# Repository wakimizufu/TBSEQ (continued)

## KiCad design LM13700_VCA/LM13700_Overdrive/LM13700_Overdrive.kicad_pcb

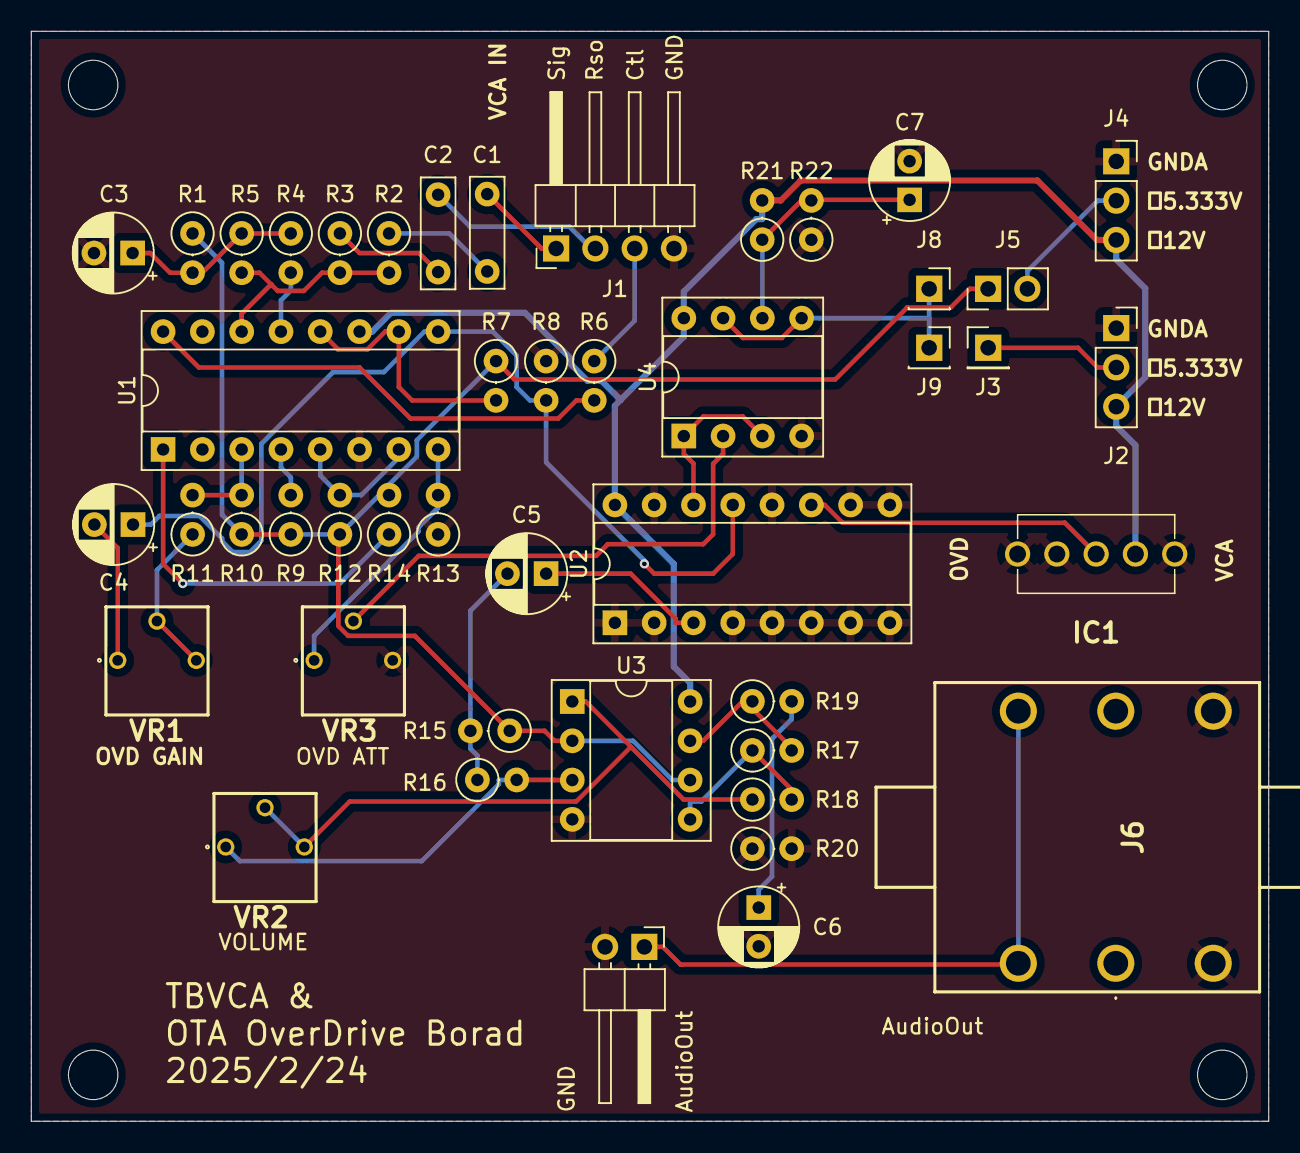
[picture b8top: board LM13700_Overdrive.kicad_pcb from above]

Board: 2 copper layers, 80.0 x 70.5 mm, 46 parts (0 on the bottom side), 36 nets.

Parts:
C1, C2: 0.01uF; C_Rect_L7.0mm_W2.0mm_P5.00mm
C3, C4: 10uF/25V; CP_Radial_D5.0mm_P2.50mm
C5, C6: 1uF/25V; CP_Radial_D5.0mm_P2.50mm
C7: 2.2uF/25V; CP_Radial_D5.0mm_P2.50mm
IC1: 2MS1T1B4VS2QES
J1: Conn_01x04; PinHeader_1x04_P2.54mm_Horizontal
J2, J4: Conn_01x03; PinSocket_1x03_P2.54mm_Vertical
J3: Conn_01x01; PinHeader_1x01_P2.54mm_Vertical
J5: Conn_01x02; PinHeader_1x02_P2.54mm_Vertical
J6: MJ-462; MJ462
J7: Conn_01x02; PinHeader_1x02_P2.54mm_Horizontal
J8, J9: Conn_01x01; PinSocket_1x01_P2.54mm_Vertical
R1, R4, R5: 2.2K; R_Axial_DIN0207_L6.3mm_D2.5mm_P2.54mm_Vertical
R2: 220K; R_Axial_DIN0207_L6.3mm_D2.5mm_P2.54mm_Vertical
R3, R15, R20: 100K; R_Axial_DIN0207_L6.3mm_D2.5mm_P2.54mm_Vertical
R6: 47K; R_Axial_DIN0207_L6.3mm_D2.5mm_P2.54mm_Vertical
R7, R12: 33K; R_Axial_DIN0207_L6.3mm_D2.5mm_P2.54mm_Vertical
R8, R13: 5K; R_Axial_DIN0207_L6.3mm_D2.5mm_P2.54mm_Vertical
R9, R10: 510; R_Axial_DIN0207_L6.3mm_D2.5mm_P2.54mm_Vertical
R11: 1K; R_Axial_DIN0207_L6.3mm_D2.5mm_P2.54mm_Vertical
R14, R16, R17, R18: 10K; R_Axial_DIN0207_L6.3mm_D2.5mm_P2.54mm_Vertical
R19: 100; R_Axial_DIN0207_L6.3mm_D2.5mm_P2.54mm_Vertical
R21: 30K; R_Axial_DIN0207_L6.3mm_D2.5mm_P2.54mm_Vertical
R22: 24K; R_Axial_DIN0207_L6.3mm_D2.5mm_P2.54mm_Vertical
U1: LM13700; DIP-16_W7.62mm_Socket
U2: 4051; DIP-16_W7.62mm_Socket
U3, U4: Opamp_Dual; DIP-8_W7.62mm_Socket
VR1, VR2, VR3: 3362P-1-104LF 100K; 3362P_1

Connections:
+5.333VA: J5.1, R1.1, R7.1, R9.1, R10.1, R12.1, R14.2, R15.1, U3.2 (-), U3.6 (-)
+12VA: IC1.3, J2.3, J4.3, R21.2, U1.11 (V+), U2.16 (VDD), U3.8 (V+), U4.8 (V+)
A+_VCA_Control: J1.3, R6.1
A+_VCA_Resonance: C2.1, J1.2
A+_VCA_Signal: C1.1, J1.1
AUDIO_OUT: C5.1, U2.3 (X)
GNDA: C3.2, C6.2, C7.2, IC1.1, IC1.MH1, IC1.MH2, J1.4, J2.1, J4.1, J6.S1, J6.SS1, J7.2, R8.1, R13.1, R20.1, R20.2, R22.1, U1.6 (V-), U2.1 (X4), U2.2 (X6), U2.4 (X7), U2.5 (X5), U2.6 (Inh), U2.7 (VEE), U2.8 (VSS), U2.9 (C), U2.10 (B), U2.12 (X3), U2.15 (X2), U3.4 (V-), U4.4 (V-), VR3.3 (CW)
unnamed: C1.2, R2.1
unnamed: C2.2, R3.1
unnamed: C3.1, R1.2, R4.1, R5.1
unnamed: C5.2, R15.2, R16.1
unnamed: C6.1, R19.2
unnamed: J2.2, J3.1
unnamed: J4.2, J5.2
unnamed: J6.T1, J6.TS1, J7.1
unnamed: J8.1, J9.1, U4.5 (+), U4.7
unnamed: R6.2, U1.16
unnamed: R7.2, U1.10, U1.12
unnamed: R12.2, U1.5, U1.7
unnamed: R14.1, U1.1
unnamed: R17.2, R19.1, U3.7
unnamed: R2.2, R3.2, R5.2, U1.14 (+)
unnamed: R4.2, U1.13 (-)
unnamed: R10.2, R11.2, U1.3 (+)
unnamed: R9.2, U1.4 (-)
unnamed: R16.2, U3.3 (+), VR2.1 (CCW)
unnamed: R17.1, R18.2, U3.5 (+)
unnamed: U4.2 (-), VR3.2 (WIPER)
unnamed: C7.1, R21.1, R22.2, U4.6 (-)
unnamed: C4.2, VR1.1 (CCW)
unnamed: R11.1, VR1.2 (WIPER), VR1.3 (CW)
unnamed: R18.1, U3.1, VR2.2 (WIPER), VR2.3 (CW)
unnamed: R13.2, U1.8, VR3.1 (CCW)
OVD_OUT: U2.14 (X1), U4.1, U4.3 (+)
SELECT: IC1.2 (2_Comm), U2.11 (A)
VCA_OUT: C4.1, R8.2, U1.9, U2.13 (X0)

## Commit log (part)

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2024-05-16 testClock
2024-05-16 addVSCode
2024-05-16 matrixLED.h
2024-05-16 matrixLED
2024-05-16 reupload TestSwLed
2024-05-16 matrixSW
2024-05-16 SwitchBox
2024-05-17 20240517
2024-05-20 #define DEBUG_ARDUINO
2024-05-20 IDE2 not support VSCode
2024-05-21 voltage
2024-05-21 vscode setting
2024-05-25 mingw&CMake
2024-05-25 VS2022_CPP
2024-05-26 VS2022 cpp/h分離
2024-05-28 DEBUG_ARDUINO
2024-05-28 arudino ソースファイル整理
2024-05-28 boradConst.h
2024-05-31 pin setup
2024-06-19 setup
2024-06-24 aurudino.h
2024-06-24 convert UTF-8
2024-06-25 add debugMode
2024-07-04 debug
2024-07-05 matrixLED&Switch
2024-07-06 32us
2024-07-08 tempo ADC
2024-07-08 tempo debug
2024-07-09 printf tempo
2024-07-09 debugmode
2024-07-11 debug mode
2024-07-12 debug debugmode
2024-07-12 sequenceList&Index
2024-07-14 debugmode スイッチ押したらLEDマトリクス点灯安定版
2024-07-16 debugmode PMW note/LED acc
2024-07-17 patternmode
2024-07-18 patern play::stop
2024-07-19 paternplay squencemap
2024-07-19 patternmode paternplay run
2024-07-20 patternmode patternplay 一通り完了版
2024-07-20 patternmode paternplay TIE
2024-07-21 patternmode paternWrite
2024-07-22 patternmode paternWrite Ver0.1
2024-07-31 TBSEQ_Borad_V1/FRAM
2024-07-31 loadFRAM
2024-08-01 FRAM WritePattern
2024-08-04 HT16K33 5VOutputBuffer
2024-08-05 HT16K33Panel
2024-08-07 HT16K33 Control
2024-08-07 replace
2024-08-08 HT16K33Panel DRC gaber
2024-08-09 powersupply
2024-08-10 analog_separate
2024-08-20 SeqBox
2024-08-21 SeqBox HT16K33 Fix
    LED表示,Switch読み取りタイミング調整済
2024-08-21 SeqBox Fix
    ステップLED点灯追加
    FRAMライブラリの呼び出しが上手く行かない?
    ⇒SeqBoxだと書き込みメソッド(_writeblock())が呼び出せない
    ⇒代替コードでI2Cコマンド送信でしても反映されず
    ⇒ただしFRAMサンプルプログラムは正常に読み書きできるので回路は問題なさそう
2024-08-22 SeqBox Fix
    ・切り分けの為 class FRAM11の内容をpanelManagerに移植した
    ・matrixSwitch::set 配列指定時に指定外の値に値設定してたので修正してFRAM書き込み確認済
    ・LENMAXを仮実装済
2024-08-22 analog_separate Fix
    DMMT3906->HN4C51J
2024-08-24 HT16K33Panel LevelConvert
    HD74LVC541A で5V->3.3Vへ変換をブレッドボードで確認済
2024-08-25 HT16K33
    MIDI RX動作確認済
2024-08-25 SeqBox Fix
    パターンライト:RUNボタンクリック時の演奏を実装
    ⇒演奏中もステップの編集が出来る様に変更
2024-08-26 SeqBox
    パターンプレイ:演奏時の開始ステップのバグ修正
2024-08-26 SeqBox update
    パターンプレイ/ライト:バンク:バンクA,B,C,Dを仮実装済
2024-08-27 SeqBox Fix
    SyncOut:内部テンポに応じた出力を実装済
    ⇒SyncInは仕様上実装を見送り
2024-08-28 SeqBox fix
    MIDIRecive:コーディング済 デバッグ待ち
2024-08-30 SeqBox Fix
    8/30に何故がコンパイルすると起動直ぐにタイマー割込みが停止してしまう？
    ⇒8/27時点のソースから徐々に切り分けしてしたら何故か正常に動く様になった
    MIDIRx:動作確認済
    SyncOut:原因切り分けの為一旦コードを除外
2024-08-31 SeqBox Fix
    SyncOut:再度実装して動作確認済
    パターンプレイ:テンポ点滅スピードを2倍に変更
2024-09-04 SeqBox fix
    ・アクセントの極性を(ON=0V OFF=5V)に変更
    ・パターンライト:RUN状態での演奏で、ゲート/スライド/アクセントがパターンプレイと異なる状態だったのを修正
2024-09-23 analog_separate fix
    実装してバグを修正
    ・VR6以外のボリュームの左右が逆なのを修正
    ・デュアルトランジスタをHN1C01FU-GRに変更
    ・VCA CA3080後の出力段のバイアス/増幅率等の設計ミスを修正
    ・入力信号のシルク位置が間違っているので修正
    ⇒それ以外は正常動作を確認済
2024-09-29 TBSEQ_Board_V2
    メインボード作成中
2024-10-03 mainboard
    PWS,Digi
2024-10-07 mainBoard
    AnInterface
2024-10-08 mainBoard
    VCO
2024-10-13 mainboard
    部品を全部配置しただけ
2024-10-13 mainborad
    DRCチェック通過
2024-10-14 mainboard & frontPanel
    コメント記入&寸法合わせ
2024-10-14 mainBoard&FrontPanel
    微修正
2024-10-21 trackMap
    trackMap作成中
2024-10-22 trackmap
    trackmap一通り書き終わり
2024-10-23 trackmap
    VC++set/getデバッグ完了
2024-10-24 modeManager
    trackmap追加中
2024-10-26 mode
    トラック関連追加
2024-10-28 trackplay
    patternplayからコピペ中
2024-10-29 trackplay
    トラックステップ追記中
2024-11-03 trackWrite
    演奏は無しで作成中
2024-11-04 trackwrite
    ビルド&デバッグ前
2024-11-05 trackplay.write
    デバッグ中
    FRAM11_test_sequenceMapとFRAM11_test_trackMapを登録
    ⇒FRAM11_test_trackMapでFRAM書き読み確認すみ
2024-11-06 trackplay,trackwrite
    コンパイル通過 デバッグ待ち
2024-11-07 modeManager
    trackPlay,trackWriteクラス生成が抜けてたので追記
2024-11-10 add_repeating_timer_us
    リピート設定にするとタイマーが停止してしまうバグ？があるので、ワンショット設定にして、割込み最後に割込み開始する様に修正した
2024-11-10 trackMap
    presetTrack()を実行
2024-11-11 trackplay
    トラックステップ/ラストステップを表示
2024-11-12 TimerCallBack&trackPlay
    タイマーコールバックが起動しない対策を実装
    トラックプレイのパターン指定の修正＆演奏中のLED表示を変更
2024-11-13 trackPlay
    トランスポート反映確認済(デバッグ出力のみ変更)
2024-11-13 trackWrite
    LED表示修正
    トランスポート設定で止まる
2024-11-14 trackwrite
    トランスポート設定のフリーズを修正
    バックSWでラストステップに飛ばないバグを修正
2024-11-17 trackwrite
    [トラックライト]
    パターン選択時のSWとLEDが食い違いを修正
    トラックライト⇒トラックプレイ切り替え時にFRAM書き込み追加
    [デバックモード]
    ・電源投入時のRUN/STOPボタン判定&LED表示を変更
2024-11-18 utilityMode
    ユーティリティーモード作成開始
2024-11-19 utilityMode
    ユーティリティーモードへ遷移する導線をコーディング済 デバッグ待ち
2024-11-20 utilityMode
    FRAM読み書きと設定反映を実装してひとまず完了
2024-11-20 SyncIn
    ピンアサインとプラグインSyncIn端子のテスト
2024-12-01 SEQBOXv2
    TB-SEQVer2向けプログラム登録しただけ
2024-12-02 SyncOut
    SyncOutの仕様をDinSync(24PPQN)に変更中
2024-12-04 SyncOut
    ざっとコーディング デバッグ待ち
2024-12-05 SyncOut&WDG
    シンクアウトが一通りデバッグ済
    パターンプレイで止まってしまうので、切り分けの為WDGをsetup(),loop()で実装
2024-12-08 SyncOut
    ・Run/Stop⇒MIDIメッセージ スタートとコンティニューどちらでもRUNする様に修正
    ・MIDI IN⇒32usecカウンタを追加してシンクアウトのテンポを設定する
2024-12-10 SyncIn
    MIDIINを参考に実装済 デバッグを行う
2024-12-14 mainBoradV2.5
    修正中
2025-03-09 AddBoard
    Ver3まで登録
2025-03-11 BoardV3
    ERCチェック済
2025-03-12 V3Board
    DualTr フットプリント変更
    配線ミス修正
    TEMPO削除⇒PanelBoardに移動
2025-03-13 V3Board
    opamp Dip8に対応
    部品配置
2025-03-15 V3Board
    アートワーク中
2025-03-16 V3Board
    アートワーク仮配置
2025-03-17 V3Board
    GNDパターン塗り済
2025-03-18 V3Board
    スペーサー穴追加
    オートルーター後
    DualTr,OPアンプは表面実装に切り替え
2025-03-19 V3Board
    DualTr OPAmp やはりDIPに変更してオートルーター前に戻す
2025-03-20 V3Board
    ERCチェック修正中
2025-03-20 V3Board
    ECRエラー全て解消
2025-03-20 V3Board
    PanelBoardを追加 オートルーター前
2025-03-22 V3Board
    panelBoardアートワーク完了 ラベル未記入
2025-03-24 V3Board
    PanelBoard⇒debugPanelBoardにして部品を全部表に出してアートワーク修正中
2025-05-04 TBSEQ3
    ハードウェアデバッグしたバージョン>mainBORAD_R1
2025-10-07 SeqBoxV2
    パターンプレイで2～8を選択⇒パターンライト⇒パターンプレイに戻ってRUNすると、次のパターンが必ず1に設定されてしまうバグを修正
2026-06-03 gitTBSEQ
    Ver4登録まで
